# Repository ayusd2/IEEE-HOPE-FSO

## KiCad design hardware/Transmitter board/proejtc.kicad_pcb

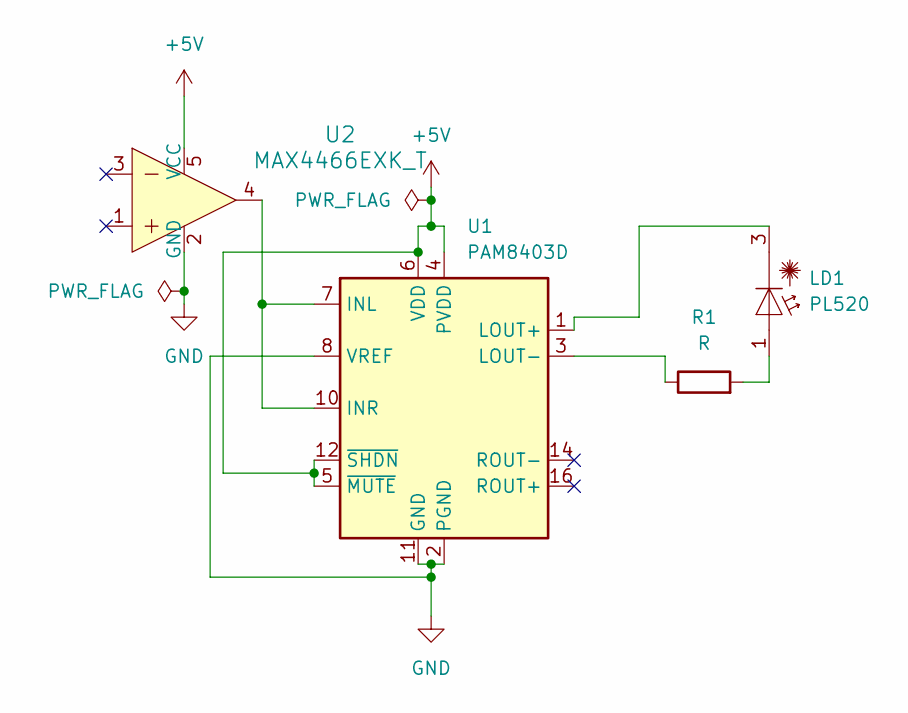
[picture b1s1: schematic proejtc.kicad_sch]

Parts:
LD1: PL520; LaserDiode_TO38ICut-3
R1: R; R_Axial_DIN0204_L3.6mm_D1.6mm_P5.08mm_Vertical
U1: PAM8403D; SOIC-16_3.9x9.9mm_P1.27mm
U2: MAX4466EXK_T; SOT-353; MPN MAX4466EXK+T; Digi-Key_PN MAX4466EXK+CT-ND

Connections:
+5V: U1.4 (PVDD), U1.5 (~MUTE), U1.6 (VDD), U1.12 (~SHDN), U1.13 (PVDD), U2.5 (VCC)
GND: U1.2 (PGND), U1.8 (VREF), U1.11 (GND), U1.15 (PGND), U2.2 (GND)
unnamed: LD1.1 (A), R1.2
unnamed: LD1.3 (C), U1.1 (LOUT+)
unnamed: U1.7 (INL), U1.10 (INR), U2.4
unnamed: R1.1, U1.3 (LOUT-)

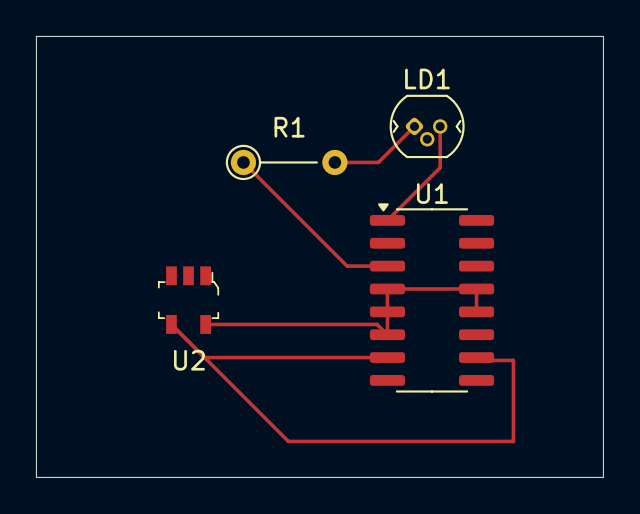
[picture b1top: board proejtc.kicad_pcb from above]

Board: 2 copper layers, 31.5 x 24.5 mm, 4 parts (0 on the bottom side), 6 nets.

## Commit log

2025-10-13 Added initial project folder structure
2025-11-03 Updated folder structure
2025-11-03 Updated folder structure and gitignore
